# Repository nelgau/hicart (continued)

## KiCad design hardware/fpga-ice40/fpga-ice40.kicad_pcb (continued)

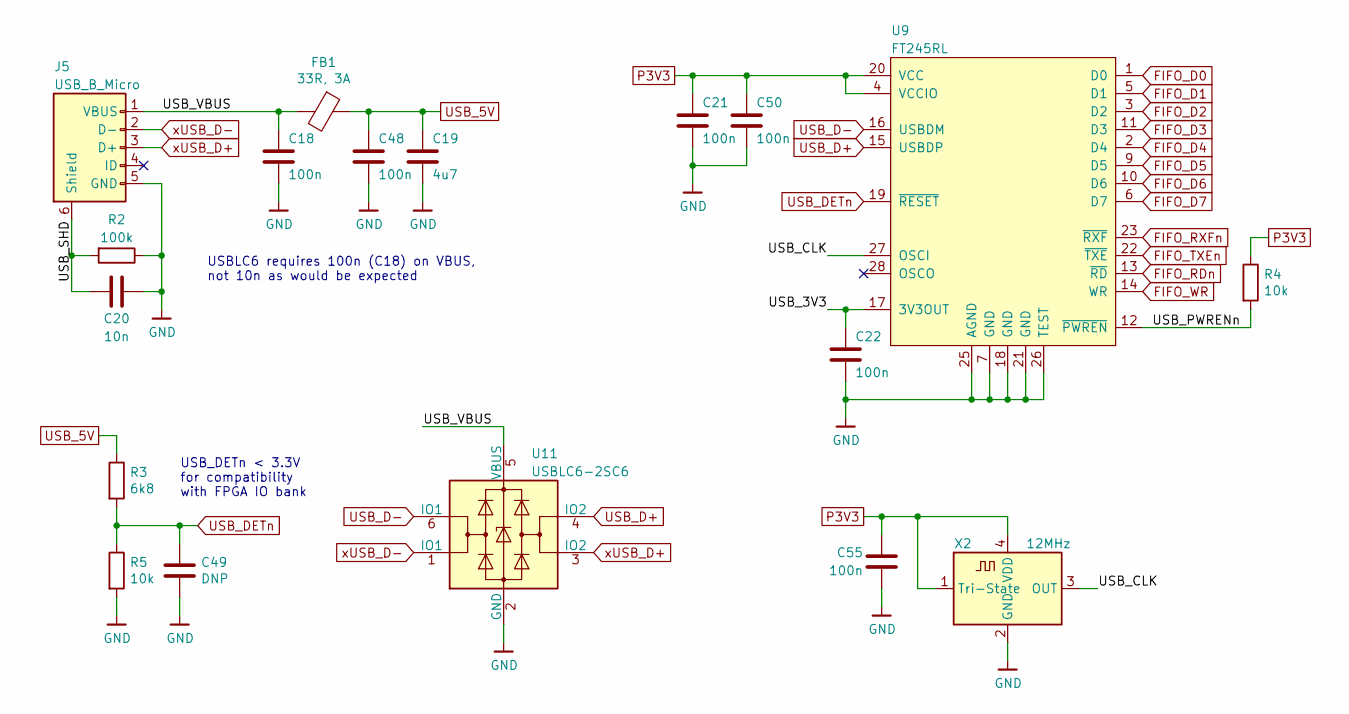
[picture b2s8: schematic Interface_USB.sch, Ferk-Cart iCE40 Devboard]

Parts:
C18, C21, C22, C48, C50, C55: 100n; C_0603_1608Metric; MPN CL10B104KB8NNNC
C19: 4u7; C_0603_1608Metric; MPN CL10A475KA8NQNC
C20: 10n; C_0603_1608Metric; MPN CL10B103KC8NNNC
C49: DNP; C_0603_1608Metric
FB1: 33R, 3A; L_0603_1608Metric; MPN BLM18PG330SN1D
J5: USB_B_Micro; USB_Micro-B_Molex_47346-0001; MPN 47346-0001
R2: 100k; R_0603_1608Metric; MPN RC0603JR-07100KL
R3: 6k8; R_0603_1608Metric; MPN RC0603FR-076K8L
R4, R5: 10k; R_0603_1608Metric; MPN RC0603FR-0710KL
U9: FT245RL; SSOP-28_5.3x10.2mm_P0.65mm; MPN FT245RL-REEL
U11: USBLC6-2SC6; SOT-23-6
X2: 12MHz; Oscillator_2.5x2.0; MPN ECS-2520MV-120-BN-TR

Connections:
/Interface_USB/USB_3V3: C22.1, U9.17 (3V3OUT)
/Interface_USB/USB_CLK: U9.27 (OSCI), X2.3 (OUT)
/Interface_USB/USB_PWRENn: R4.2, U9.12 (~PWREN)
/Interface_USB/USB_SHD: C20.1, J5.6 (Shield), R2.2
/Interface_USB/USB_VBUS: C18.1, FB1.2, J5.1 (VBUS), U11.5 (VBUS)
FIFO_D0: U9.1 (D0); also elsewhere on the board
FIFO_D1: U9.5 (D1); also elsewhere on the board
FIFO_D2: U9.3 (D2); also elsewhere on the board
FIFO_D3: U9.11 (D3); also elsewhere on the board
FIFO_D4: U9.2 (D4); also elsewhere on the board
FIFO_D5: U9.9 (D5); also elsewhere on the board
FIFO_D6: U9.10 (D6); also elsewhere on the board
FIFO_D7: U9.6 (D7); also elsewhere on the board
FIFO_RDn: U9.13 (~RD); also elsewhere on the board
FIFO_RXFn: U9.23 (~RXF); also elsewhere on the board
FIFO_TXEn: U9.22 (~TXE); also elsewhere on the board
FIFO_WR: U9.14 (WR); also elsewhere on the board
GND: C18.2, C19.2, C20.2, C21.2, C22.2, C48.2, C49.2, C50.2, C55.2, J5.5 (GND), R2.1, R5.2, U9.7 (GND), U9.18 (GND), U9.21 (GND), U9.25 (AGND), U9.26 (TEST), U11.2 (GND), X2.2 (GND); also elsewhere on the board
P3V3: C21.1, C50.1, C55.1, R4.1, U9.4 (VCCIO), U9.20 (VCC), X2.1 (Tri-State), X2.4 (VDD); also elsewhere on the board
USB_5V: C19.1, C48.1, FB1.1, R3.1; also elsewhere on the board
USB_D+: U9.15 (USBDP), U11.4 (IO2)
USB_D-: U9.16 (USBDM), U11.6 (IO1)
USB_DETn: C49.1, R3.2, R5.1, U9.19 (~RESET); also elsewhere on the board
xUSB_D+: J5.3 (D+), U11.3 (IO2)
xUSB_D-: J5.2 (D-), U11.1 (IO1)

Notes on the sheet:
USB_DETn < 3.3V for compatibility with FPGA IO bank
USBLC6 requires 100n (C18) on VBUS, not 10n as would be expected

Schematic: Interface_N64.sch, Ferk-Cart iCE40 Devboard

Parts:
C54: 100n; C_0603_1608Metric
J6: Conn_02x20_Odd_Even; PinHeader_2x20_P2.54mm_Horizontal; MPN C124369
RN4, RN5, RN6, RN7, RN8, RN9: 33R, 1%; R_Array_Convex_4x0603; MPN YC164-FR-0733RL

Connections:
GND: C54.2, J6.12, J6.14, J6.16, J6.18, J6.30; also elsewhere on the board
N64_3V3: J6.13, J6.15, J6.17; also elsewhere on the board
N64_AD0: RN4.7 (R2.2); also elsewhere on the board
N64_AD1: RN4.5 (R4.2); also elsewhere on the board
N64_AD2: RN6.7 (R2.2); also elsewhere on the board
N64_AD3: RN6.5 (R4.2); also elsewhere on the board
N64_AD4: RN5.7 (R2.2); also elsewhere on the board
N64_AD5: RN5.5 (R4.2); also elsewhere on the board
N64_AD6: RN7.8 (R1.2); also elsewhere on the board
N64_AD7: RN7.6 (R3.2); also elsewhere on the board
N64_AD8: RN7.5 (R4.2); also elsewhere on the board
N64_AD9: RN7.7 (R2.2); also elsewhere on the board
N64_AD10: RN5.6 (R3.2); also elsewhere on the board
N64_AD11: RN5.8 (R1.2); also elsewhere on the board
N64_AD12: RN6.6 (R3.2); also elsewhere on the board
N64_AD13: RN6.8 (R1.2); also elsewhere on the board
N64_AD14: RN4.6 (R3.2); also elsewhere on the board
N64_AD15: RN4.8 (R1.2); also elsewhere on the board
N64_ALE_H: RN8.5 (R4.2); also elsewhere on the board
N64_ALE_L: RN8.8 (R1.2); also elsewhere on the board
N64_COLD_RESETn: RN9.7 (R2.2); also elsewhere on the board
N64_OS_EVENTn: RN9.8 (R1.2); also elsewhere on the board
N64_READn: RN8.6 (R3.2); also elsewhere on the board
N64_WRITEn: RN8.7 (R2.2); also elsewhere on the board
P3V3: C54.1; also elsewhere on the board
xN64_AD0: J6.39, RN4.2 (R2.1)
xN64_AD1: J6.37, RN4.4 (R4.1)
xN64_AD2: J6.35, RN6.2 (R2.1)
xN64_AD3: J6.33, RN6.4 (R4.1)
xN64_AD4: J6.25, RN5.2 (R2.1)
xN64_AD5: J6.23, RN5.4 (R4.1)
xN64_AD6: J6.21, RN7.1 (R1.1)
xN64_AD7: J6.19, RN7.3 (R3.1)
xN64_AD8: J6.20, RN7.4 (R4.1)
xN64_AD9: J6.22, RN7.2 (R2.1)
xN64_AD10: J6.24, RN5.3 (R3.1)
xN64_AD11: J6.26, RN5.1 (R1.1)
xN64_AD12: J6.34, RN6.3 (R3.1)
xN64_AD13: J6.36, RN6.1 (R1.1)
xN64_AD14: J6.38, RN4.3 (R3.1)
xN64_AD15: J6.40, RN4.1 (R1.1)
xN64_ALE_H: J6.27, RN8.4 (R4.1)
xN64_ALE_L: J6.31, RN8.1 (R1.1)
xN64_COLD_RESETn: J6.5, RN9.2 (R2.1)
xN64_OS_EVENTn: J6.6, RN9.1 (R1.1)
xN64_READn: J6.28, RN8.3 (R3.1)
xN64_WRITEn: J6.32, RN8.2 (R2.1)

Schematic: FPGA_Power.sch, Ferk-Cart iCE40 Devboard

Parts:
C23, C30, C42: 10u; C_0603_1608Metric; MPN CL10A106MQ8NNNC
C24, C46: 1u; C_0603_1608Metric; MPN CL10A105KB8NNNC
C25, C26, C27, C28, C29, C31, C33, C34, C35, C36, C37, C38, C39, C40, C41, C43: 100n; C_0603_1608Metric; MPN CL10B104KB8NNNC
C32: 10u; C_0805_2012Metric; MPN CL21A106KAYNNNE
C45, C47: 10n; C_0603_1608Metric; MPN CL10B103KC8NNNC
D1: ~~800mVf; D_SOD-123F; MPN SBR2M60S1F-7
R6, R7: 100R; R_0603_1608Metric; MPN RC0603FR-07100RL
U1: iCE40HX4K-TQ144; TQFP-144_20x20mm_P0.5mm; MPN iCE40HX4K-TQ144

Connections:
GND: C23.2, C24.2, C25.2, C26.2, C27.2, C28.2, C29.2, C32.2, C33.2, C34.2, C35.2, C36.2, C37.2, C38.2, C39.2, C40.2, C41.2, C45.2, C46.2, C47.2, U1.5 (GND), U1.13 (GND), U1.14 (GND), U1.59 (GND), U1.69 (GND), U1.86 (GND), U1.103 (GND), U1.132 (GND), U1.140 (GND); also elsewhere on the board
P1V2: C23.1, C24.1, C25.1, C26.1, C27.1, C28.1, C45.1, R6.2, R7.2, U1.27 (VCC), U1.40 (VCC), U1.92 (VCC), U1.111 (VCC); also elsewhere on the board
P3V3: C32.1, C33.1, C34.1, C35.1, C36.1, C37.1, C38.1, C39.1, C40.1, C41.1, C46.1, C47.1, D1.2 (A), U1.6 (VCCIO_3), U1.30 (VCCIO_3), U1.46 (VCCIO_2), U1.57 (VCCIO_2), U1.72 (VCC_SPI), U1.89 (VCCIO_1), U1.100 (VCCIO_1), U1.123 (VCCIO_0), U1.131 (VCCIO_0); also elsewhere on the board
VCC2V5: C29.1, D1.1 (K), U1.108 (VPP_2V5)
VCCGND0: C30.2, C31.2, U1.53 (GNDPLL0)
VCCGND1: C42.2, C43.2, U1.127 (GNDPLL1)
VCCPLL0: C30.1, C31.1, R6.1, U1.54 (VCCPLL0)
VCCPLL1: C42.1, C43.1, R7.1, U1.126 (VCCPLL1)

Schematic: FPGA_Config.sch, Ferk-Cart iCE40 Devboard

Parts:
C44: 100n; C_0603_1608Metric; MPN CL10B104KB8NNNC
RN10: 10k; R_Array_Convex_4x0603; MPN YC164-JR-0710KL
U1: iCE40HX4K-TQ144; TQFP-144_20x20mm_P0.5mm; MPN iCE40HX4K-TQ144
U10: MC74HC1G08DTT1G; SOT-23-5; MPN MC74HC1G08DTT1G
X1: 50MHz; Oscillator_2.5x2.0; MPN ECS-2520MV-500-BN-TR

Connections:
CLK_50MHZ: X1.3 (OUT); also elsewhere on the board
CONFIG_CRESETn: RN10.3, U10.2; also elsewhere on the board
CONFIG_MISO|IO1: U1.68 (IOB_106_SDI); also elsewhere on the board
CONFIG_MOSI|IO0: U1.67 (IOB_105_SDO); also elsewhere on the board
CONFIG_SCK: U1.70 (IOB_107_SCK); also elsewhere on the board
CONFIG_SSn: U1.71 (IOB_108_SS); also elsewhere on the board
FLASH_CRESETn: RN10.2, U10.1; also elsewhere on the board
FPGA_CDONE: RN10.1, U1.65 (CDONE); also elsewhere on the board
FPGA_CRESETn: RN10.4, U1.66 (~CRESET_B), U10.4
GND: C44.2, U10.3 (GND), X1.2 (GND); also elsewhere on the board
P3V3: C44.1, RN10.5, RN10.6, RN10.7, RN10.8, U10.5 (VCC), X1.1 (Tri-State), X1.4 (VDD); also elsewhere on the board

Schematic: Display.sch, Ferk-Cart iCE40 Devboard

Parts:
D2, D3, D4, D5, D6, D7: Green; LED_0603_1608Metric; MPN LTST-C190GKT
Q1: 2N7002H-7; SOT-23; MPN 2N7002H-7
R10, R13: 1k; R_0603_1608Metric; MPN RC0603JR-071KL
R11: 1k; R_Array_Convex_4x0603; MPN YC164-JR-071KL

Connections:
FPGA_CDONE: Q1.1 (G); also elsewhere on the board
GND: D3.1 (K), D4.1 (K), D5.1 (K), D6.1 (K), D7.1 (K), Q1.2 (S); also elsewhere on the board
LED_D0: R11.5; also elsewhere on the board
LED_D1: R11.6; also elsewhere on the board
LED_D2: R11.7; also elsewhere on the board
LED_D3: R11.8; also elsewhere on the board
unnamed: D2.1 (K), Q1.3 (D)
unnamed: D2.2 (A), R10.2
unnamed: D3.2 (A), R11.4
unnamed: D4.2 (A), R11.3
unnamed: D5.2 (A), R11.2
unnamed: D6.2 (A), R11.1
unnamed: D7.2 (A), R13.2
P3V3: R10.1, R13.1; also elsewhere on the board

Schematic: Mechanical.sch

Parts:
FID1, FID2: Fiducial; Fiducial_1mm_Mask2mm
SYM1: Nelgau-Logo; Nelgau-Logo_5.2x1.7mm_SilkScreen

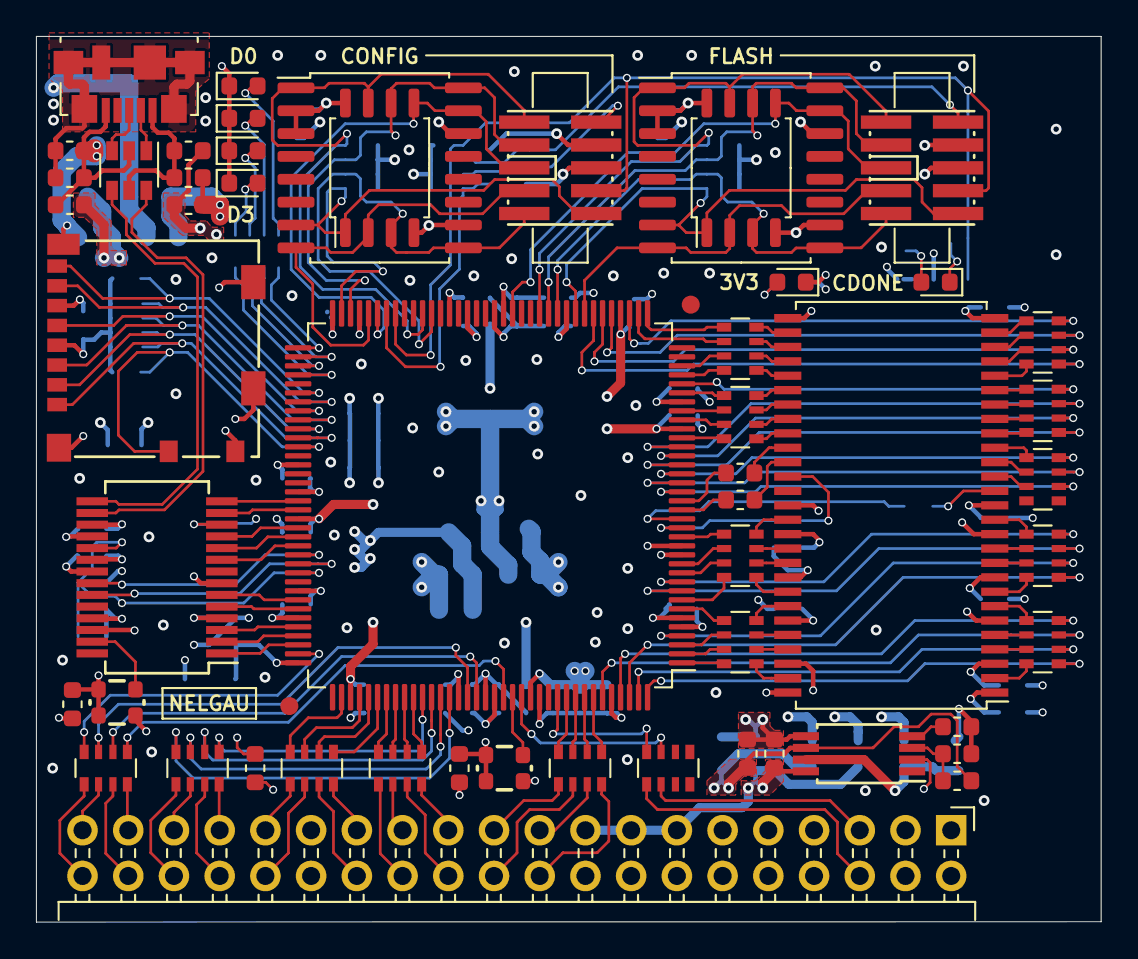
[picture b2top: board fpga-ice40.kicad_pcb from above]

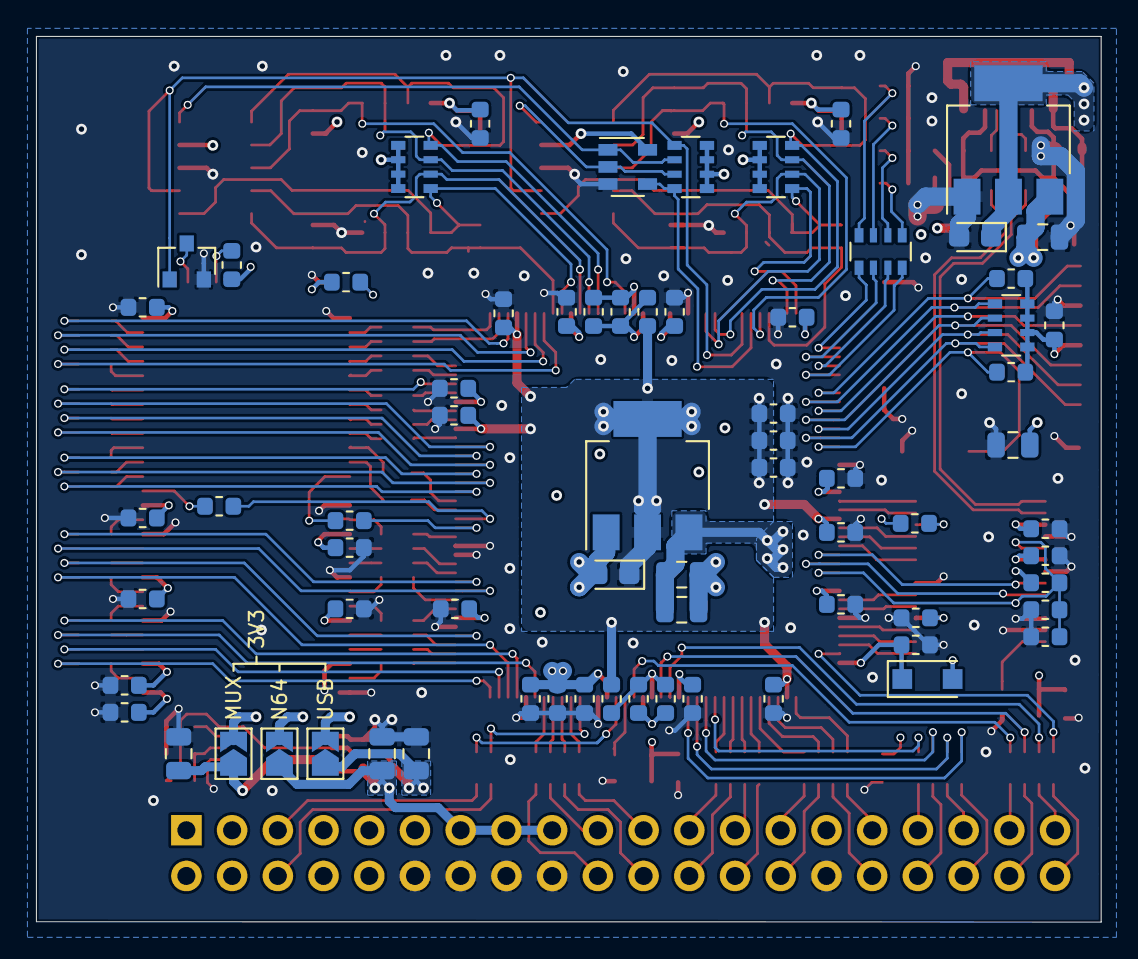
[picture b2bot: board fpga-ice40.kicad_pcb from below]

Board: 4 copper layers, 59.2 x 49.2 mm, 126 parts (70 on the bottom side), 193 nets.

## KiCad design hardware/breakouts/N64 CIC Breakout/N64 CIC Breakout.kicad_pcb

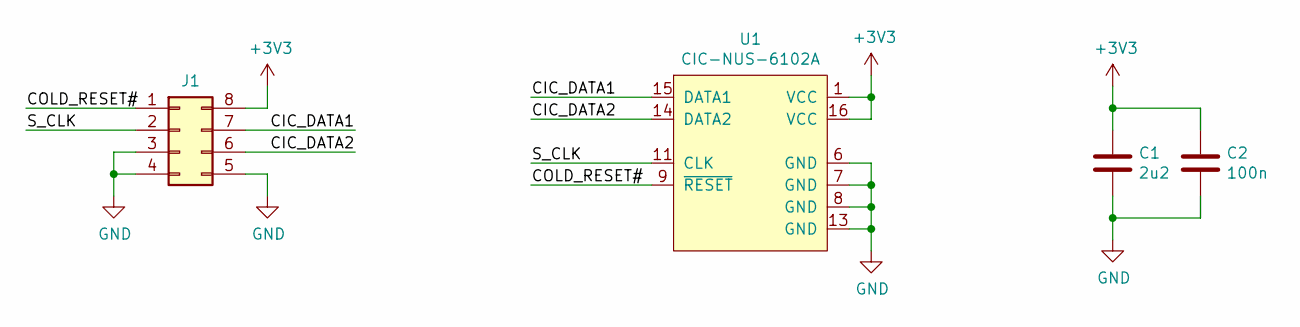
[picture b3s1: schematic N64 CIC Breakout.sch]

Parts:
C1: 2u2; C_0805_2012Metric
C2: 100n; C_0805_2012Metric
J1: Conn_02x04_Counter_Clockwise; PinHeader_2x04_P2.54mm_Horizontal
U1: CIC-NUS-6102A; DIP-16_W7.62mm_Socket

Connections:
+3V3: C1.1, C2.1, J1.8, U1.1 (VCC), U1.16 (VCC)
/CIC_DATA1: J1.7, U1.15 (DATA1)
/CIC_DATA2: J1.6, U1.14 (DATA2)
/COLD_RESET#: J1.1, U1.9 (~RESET)
/S_CLK: J1.2, U1.11 (CLK)
GND: C1.2, C2.2, J1.3, J1.4, J1.5, U1.6 (GND), U1.7 (GND), U1.8 (GND), U1.13 (GND)

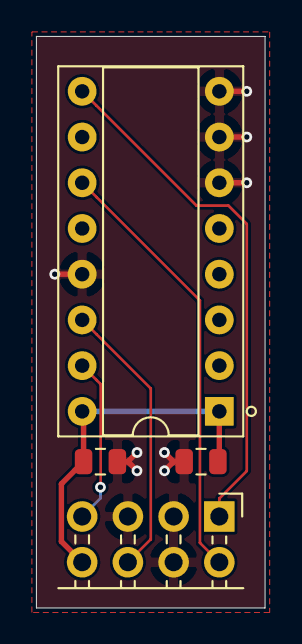
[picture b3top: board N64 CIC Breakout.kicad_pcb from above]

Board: 2 copper layers, 12.7 x 31.8 mm, 4 parts (0 on the bottom side), 6 nets.

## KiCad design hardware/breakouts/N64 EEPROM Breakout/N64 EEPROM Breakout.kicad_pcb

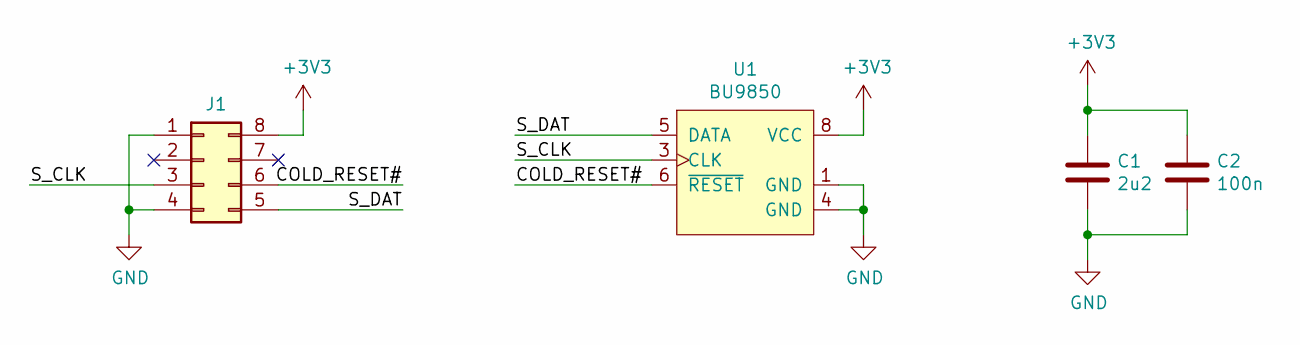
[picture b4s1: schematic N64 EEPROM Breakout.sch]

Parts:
C1: 2u2; C_0805_2012Metric
C2: 100n; C_0805_2012Metric
J1: Conn_02x04_Counter_Clockwise; PinHeader_2x04_P2.54mm_Horizontal
U1: BU9850; DIP-8_W7.62mm_Socket

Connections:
+3V3: C1.1, C2.1, J1.8, U1.8 (VCC)
/COLD_RESET#: J1.6, U1.6 (~RESET)
/S_CLK: J1.3, U1.3 (CLK)
/S_DAT: J1.5, U1.5 (DATA)
GND: C1.2, C2.2, J1.1, J1.4, U1.1 (GND), U1.4 (GND)

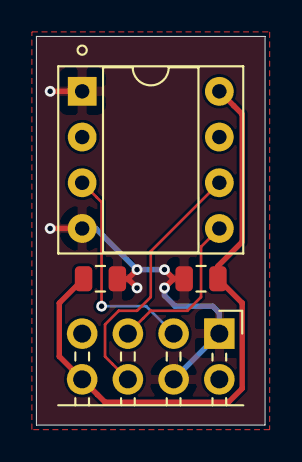
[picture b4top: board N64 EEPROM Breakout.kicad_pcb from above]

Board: 2 copper layers, 12.7 x 21.6 mm, 4 parts (0 on the bottom side), 5 nets.

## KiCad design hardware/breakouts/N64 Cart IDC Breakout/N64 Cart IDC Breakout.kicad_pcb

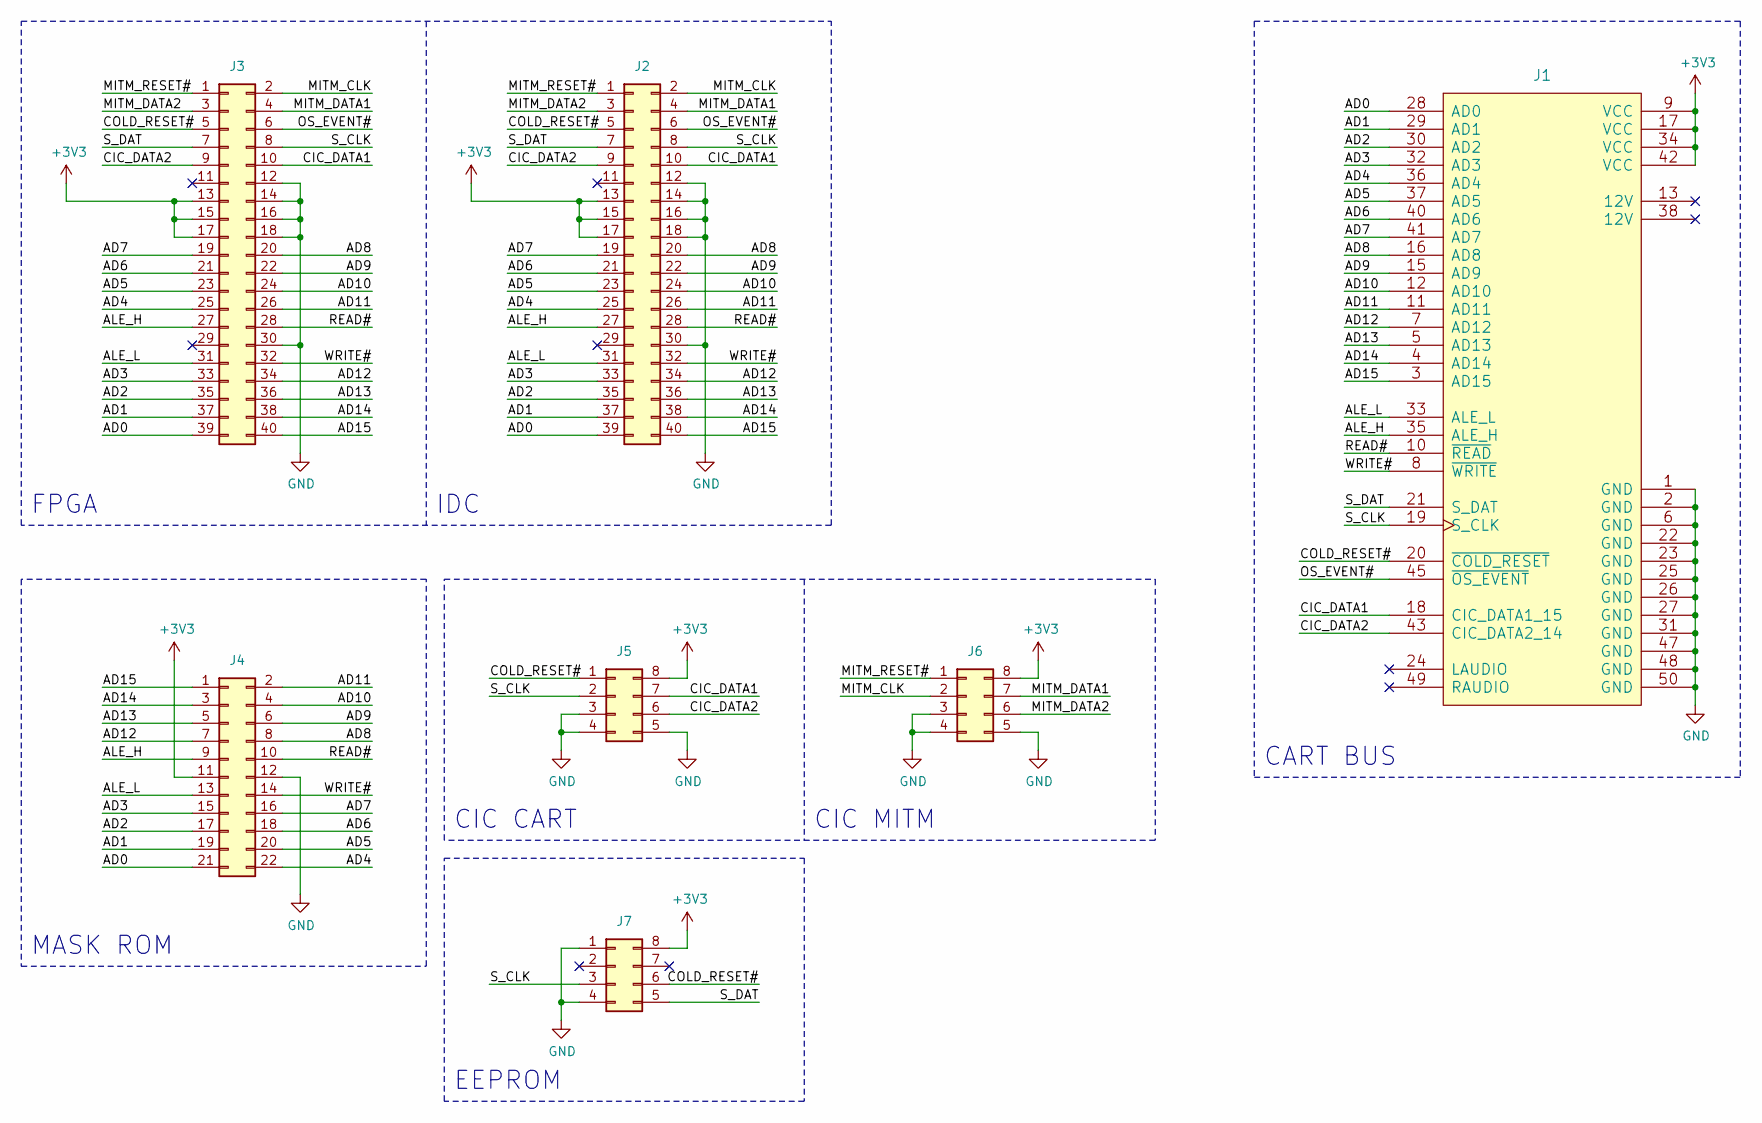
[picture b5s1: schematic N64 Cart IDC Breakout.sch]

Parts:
J1: N64_Cartridge_CardEdge
J2: Conn_02x20_Odd_Even; IDC-Header_2x20_P2.54mm_Vertical
J3: Conn_02x20_Odd_Even; PinSocket_2x20_P2.54mm_Horizontal
J4: Conn_02x11_Odd_Even; PinSocket_2x11_P2.54mm_Horizontal
J5, J6, J7: Conn_02x04_Counter_Clockwise; PinSocket_2x04_P2.54mm_Horizontal

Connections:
+3V3: J1.9 (VCC), J1.17 (VCC), J1.34 (VCC), J1.42 (VCC), J2.13, J2.15, J2.17, J3.13, J3.15, J3.17, J4.11, J5.8, J6.8, J7.8
/AD0: J1.28 (AD0), J2.39, J3.39, J4.21
/AD1: J1.29 (AD1), J2.37, J3.37, J4.19
/AD2: J1.30 (AD2), J2.35, J3.35, J4.17
/AD3: J1.32 (AD3), J2.33, J3.33, J4.15
/AD4: J1.36 (AD4), J2.25, J3.25, J4.22
/AD5: J1.37 (AD5), J2.23, J3.23, J4.20
/AD6: J1.40 (AD6), J2.21, J3.21, J4.18
/AD7: J1.41 (AD7), J2.19, J3.19, J4.16
/AD8: J1.16 (AD8), J2.20, J3.20, J4.8
/AD9: J1.15 (AD9), J2.22, J3.22, J4.6
/AD10: J1.12 (AD10), J2.24, J3.24, J4.4
/AD11: J1.11 (AD11), J2.26, J3.26, J4.2
/AD12: J1.7 (AD12), J2.34, J3.34, J4.7
/AD13: J1.5 (AD13), J2.36, J3.36, J4.5
/AD14: J1.4 (AD14), J2.38, J3.38, J4.3
/AD15: J1.3 (AD15), J2.40, J3.40, J4.1
/ALE_H: J1.35 (ALE_H), J2.27, J3.27, J4.9
/ALE_L: J1.33 (ALE_L), J2.31, J3.31, J4.13
/CIC_DATA1: J1.18 (CIC_DATA1_15), J2.10, J3.10, J5.7
/CIC_DATA2: J1.43 (CIC_DATA2_14), J2.9, J3.9, J5.6
/COLD_RESET#: J1.20 (~COLD_RESET), J2.5, J3.5, J5.1, J7.6
/MITM_CLK: J2.2, J3.2, J6.2
/MITM_DATA1: J2.4, J3.4, J6.7
/MITM_DATA2: J2.3, J3.3, J6.6
/MITM_RESET#: J2.1, J3.1, J6.1
/OS_EVENT#: J1.45 (~OS_EVENT), J2.6, J3.6
/READ#: J1.10 (~READ), J2.28, J3.28, J4.10
/S_CLK: J1.19 (S_CLK), J2.8, J3.8, J5.2, J7.3
/S_DAT: J1.21 (S_DAT), J2.7, J3.7, J7.5
/WRITE#: J1.8 (~WRITE), J2.32, J3.32, J4.14
GND: J1.1 (GND), J1.2 (GND), J1.6 (GND), J1.22 (GND), J1.23 (GND), J1.25 (GND), J1.26 (GND), J1.27 (GND), J1.31 (GND), J1.47 (GND), J1.48 (GND), J1.50 (GND), J2.12, J2.14, J2.16, J2.18, J2.30, J3.12, J3.14, J3.16, J3.18, J3.30, J4.12, J5.3, J5.4, J5.5, J6.3, J6.4, J6.5, J7.1, J7.4

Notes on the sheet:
FPGA
IDC
CIC CART
CIC MITM
MASK ROM
EEPROM
CART BUS

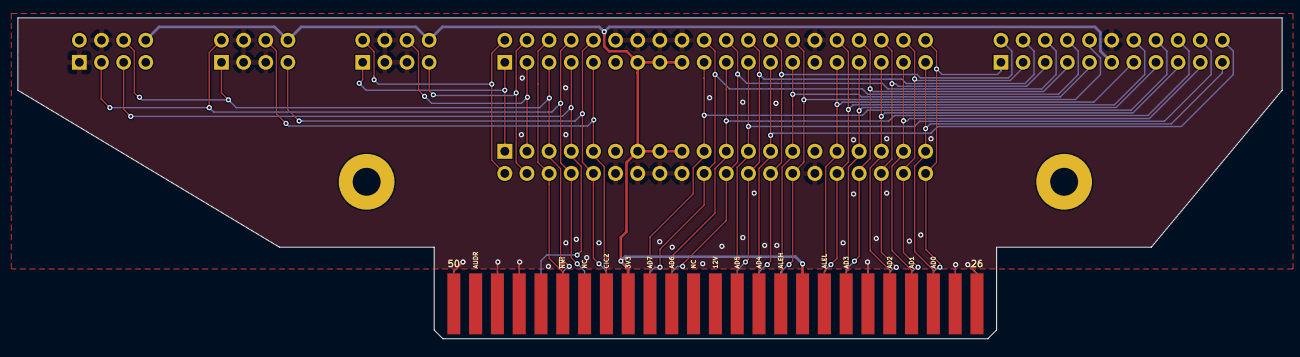
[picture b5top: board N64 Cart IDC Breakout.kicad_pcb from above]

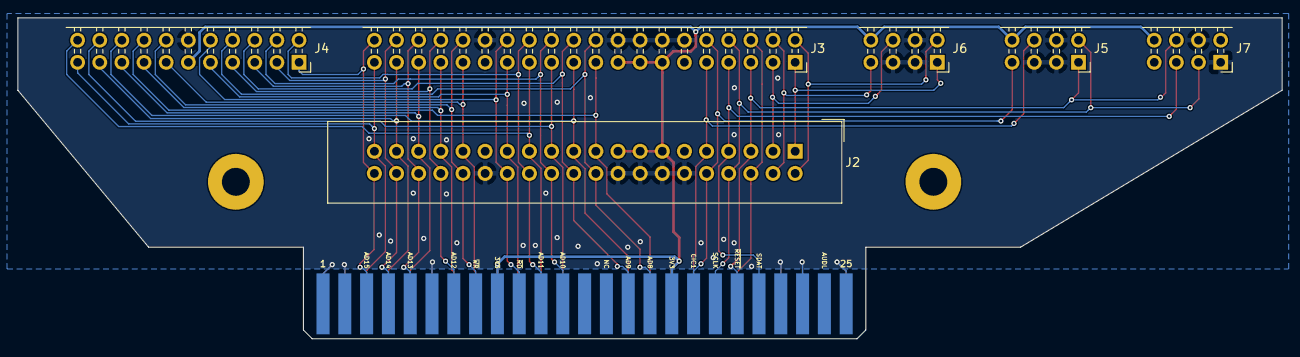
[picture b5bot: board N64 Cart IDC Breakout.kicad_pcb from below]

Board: 2 copper layers, 145.0 x 36.8 mm, 9 parts (6 on the bottom side), 32 nets.

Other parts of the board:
M1, M2: MountingHole_3.2mm_M3_Pad

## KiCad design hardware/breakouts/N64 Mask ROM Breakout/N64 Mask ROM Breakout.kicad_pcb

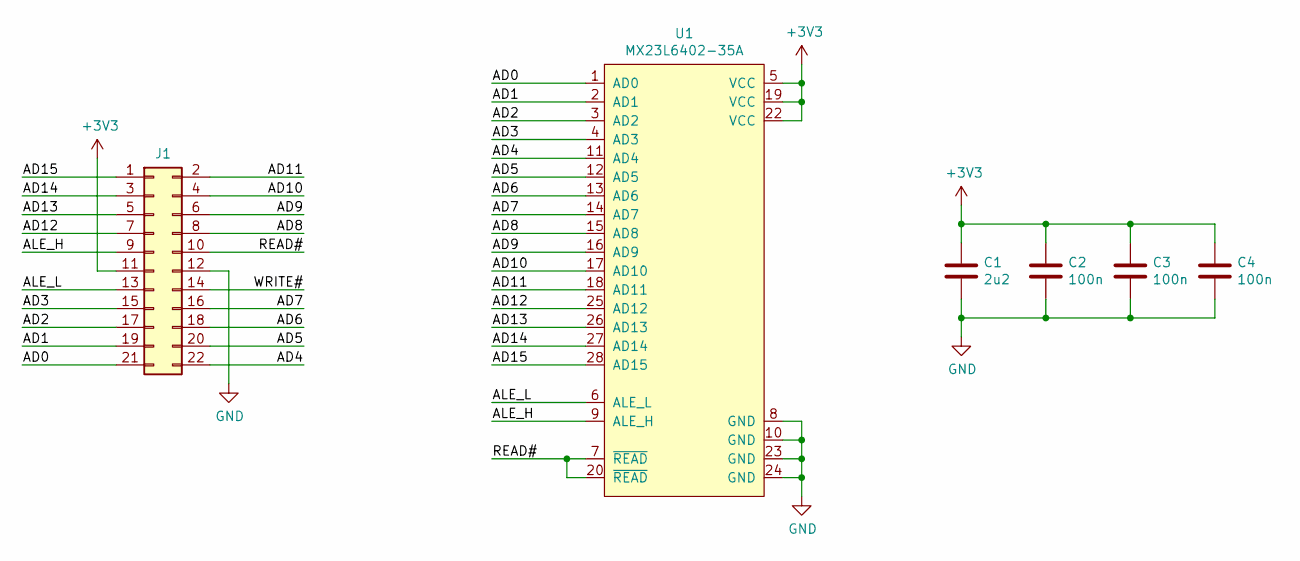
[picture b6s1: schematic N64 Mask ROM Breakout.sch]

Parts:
C1: 2u2; C_0805_2012Metric
C2, C3, C4: 100n; C_0805_2012Metric
J1: Conn_02x11_Odd_Even; PinHeader_2x11_P2.54mm_Horizontal
U1: MX23L6402-35A; DIP-28_W15.24mm_Socket

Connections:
+3V3: C1.1, C2.1, C3.1, C4.1, J1.11, U1.5 (VCC), U1.19 (VCC), U1.22 (VCC)
/AD0: J1.21, U1.1 (AD0)
/AD1: J1.19, U1.2 (AD1)
/AD2: J1.17, U1.3 (AD2)
/AD3: J1.15, U1.4 (AD3)
/AD4: J1.22, U1.11 (AD4)
/AD5: J1.20, U1.12 (AD5)
/AD6: J1.18, U1.13 (AD6)
/AD7: J1.16, U1.14 (AD7)
/AD8: J1.8, U1.15 (AD8)
/AD9: J1.6, U1.16 (AD9)
/AD10: J1.4, U1.17 (AD10)
/AD11: J1.2, U1.18 (AD11)
/AD12: J1.7, U1.25 (AD12)
/AD13: J1.5, U1.26 (AD13)
/AD14: J1.3, U1.27 (AD14)
/AD15: J1.1, U1.28 (AD15)
/ALE_H: J1.9, U1.9 (ALE_H)
/ALE_L: J1.13, U1.6 (ALE_L)
/READ#: J1.10, U1.7 (~READ), U1.20 (~READ)
/WRITE#: J1.14
GND: C1.2, C2.2, C3.2, C4.2, J1.12, U1.8 (GND), U1.10 (GND), U1.23 (GND), U1.24 (GND)

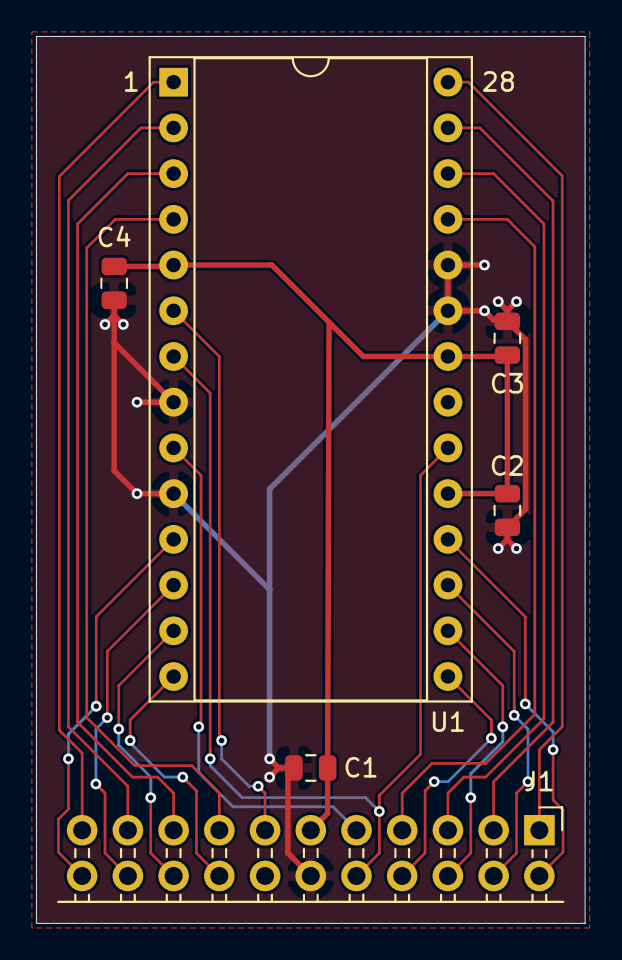
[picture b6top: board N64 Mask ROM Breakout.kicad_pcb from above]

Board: 2 copper layers, 30.5 x 49.3 mm, 6 parts (0 on the bottom side), 21 nets.

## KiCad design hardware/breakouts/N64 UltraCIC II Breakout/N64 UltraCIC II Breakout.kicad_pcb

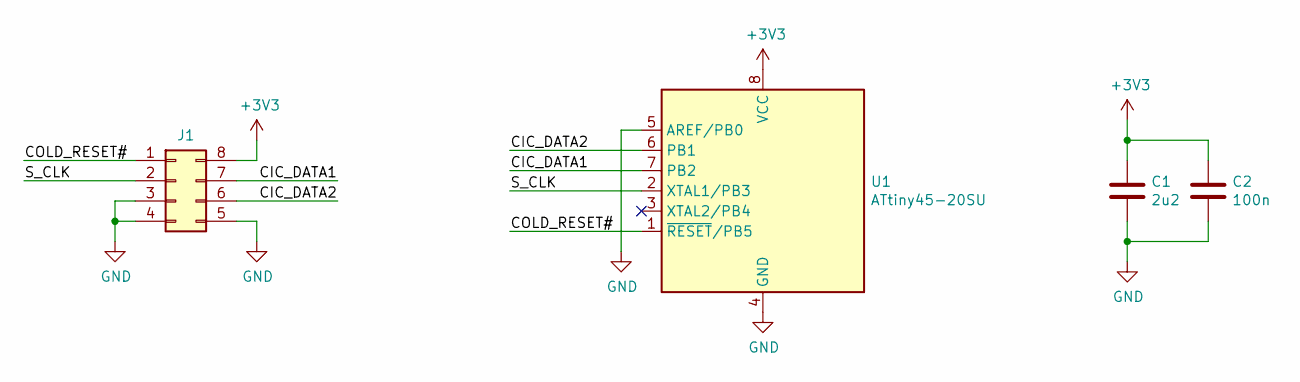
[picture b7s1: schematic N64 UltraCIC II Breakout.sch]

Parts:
C1: 2u2; C_0805_2012Metric
C2: 100n; C_0805_2012Metric
J1: Conn_02x04_Counter_Clockwise; PinHeader_2x04_P2.54mm_Horizontal
U1: ATtiny45-20SU; SOIJ-8_5.3x5.3mm_P1.27mm

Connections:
+3V3: C1.1, C2.1, J1.8, U1.8 (VCC)
/CIC_DATA1: J1.7, U1.7 (PB2)
/CIC_DATA2: J1.6, U1.6 (PB1)
/COLD_RESET#: J1.1, U1.1 (~RESET~/PB5)
/S_CLK: J1.2, U1.2 (XTAL1/PB3)
GND: C1.2, C2.2, J1.3, J1.4, J1.5, U1.4 (GND), U1.5 (AREF/PB0)

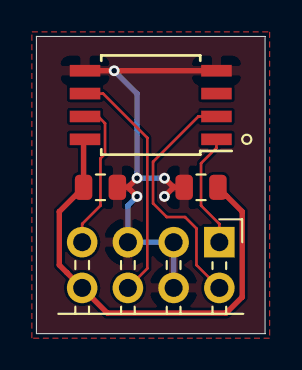
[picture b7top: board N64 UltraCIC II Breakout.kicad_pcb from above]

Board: 2 copper layers, 12.7 x 16.5 mm, 4 parts (0 on the bottom side), 6 nets.

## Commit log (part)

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2020-11-29 Update 'nelgau' library
2020-11-29 Substitute QE=1 config flash to keep boot time as short as possible
2020-11-29 Add configuration done LED
2020-11-30 Add power rail test points to schematic
2020-11-30 Fix the configuration flash's decoupling capacitor
2020-11-30 Add testpoints for clock oscillator outputs
2020-11-30 Layout testpoints for power rails and clock oscillators
2020-12-04 Connect feedback testpoints to resistor divider
2021-01-03 Use 0402 package for all 4u7 bypass capacitors
2021-01-06 Don't stuff the net name into test point values
2021-01-06 Enlarge test points to 1mm diameter
2021-01-06 Clarify pull-up design for configuration flash and FPGA reset signal
2021-01-06 Add header for injecting 3V3 rail without populating USB_3V3 regulator and power mux
2021-01-22 Reassign symbols that were rescued during update
2021-01-24 Assign MPN for all other components except oscillators
2021-01-25 Connect FT2232HQ center pad to ground
2021-01-25 Added a copper poor for the sheild of the USB connector
2021-01-26 Update PCB is reflect changes to schematic
2021-01-29 Place 1u decoupling caps near hyperram
2021-01-29 Assign MPN for hyperram device
2021-01-29 Add ground test point for hyperram interface
2021-01-30 Replace 2.5x2.0mm oscillators with SiT2001B SOT23-5 oscillators
2021-01-30 Set solder paste absolute clearance to 0
2021-01-30 Add zones for USB_3V3 and N64_3V3 terminations
2021-01-30 Output production gerbers for RevA
2021-01-30 Regenerate revA gerbers
2022-01-29 Import gateware and firmware from the minerva-test repo
2022-01-29 Ignore traces/ directory for now
2022-01-29 Clarify ecppack_opts override
2022-01-30 Reenable main CIC output test
2022-01-30 Update README with new name and hero image
2022-01-30 Use PLL generator instead of hardcoding EHXPLLL values
2022-01-30 Move ECP5PLL generator to vendor dir
2022-04-14 Correct typo during vendoring of ECP5PLL generator
2022-10-05 Fix lambdasoc bios submodule cloning issue
    This commit forks lambdasoc and updates its lambdasoc-bios submodule to HEAD.
    A submodule of lambdasoc, lambdasoc-bios, itself includes a submodule from
    the git.llvm.org hierarchy, compiler_rt. After the LLVM project moved its
    repositories to Github, this reference has rotted into a redirect loop. The
    issue was fixed in lambdasoc-bios. Unfortunately, lambdasoc hasn't yet been
    updated to reference the fix.
2022-10-05 Downgrade libusb1 to 1.9.3, the last non-yanked version before 2.0.0
2022-10-05 Add cocotb and cocotb-test dependencies
2022-10-06 Update pytest to fix assertion issue under Py3.10
    See https://github.com/pytest-dev/pytest/issues/8539
2022-10-06 Provisionary test harness based on amaranth-cocotb
2022-10-06 Update nextpnr-ecp5 build time estimate
2022-10-06 Rename README.rst to README.md
2022-10-06 Document icarus-verilog package dependency
2022-10-06 Add instructions to build python with --enable-shared
2022-10-06 Simplify cocotb-test runner as we don't need to subclass Icarus
2022-10-06 Empty out synonyms in the hicart.test module root
2022-10-06 Fix failing test in hicart.n64.pi
    The initiator's wishbone bus uses the stall feature. To be connectable, the
    DUT's decoder needs to support that feature as well.
2022-10-06 Fix failing test in hicart.n64.ad16
    The Pysim-style test cases for this module predate the implementation of
    the deep synchronizer for the address-data lines. Additionally, on read,
    the high and low words were swapped, as presented to the AD16 bus.
    These failures are a good argument for why it must be possible to run
    the entire test suite easily and with a single command.
2022-10-06 Divide the test infrastructure into pysim and cocotb modules
2022-10-06 Don't generate waveforms unless GENERATE_VCDS is set
2022-10-06 Improve cocotb test harness readability
2022-10-07 Add enjoydigital/litesdcard dependency
2022-10-07 Begin to integrate lambdaconcept's LiteX core wrapper idea
2022-10-07 Slightly hacky way to generate i/o/oe-style IO
2022-10-08 Passthrough SD interface pins to LiteSDCard core instance
2022-10-08 Move litesdcard generator to vendor directory
2022-10-10 Remove of the module name introspection magic from cocotb testcases
2022-10-10 Validate cocotb test concept with a basic AD16 driver coroutine
2022-10-10 Simulate the platform's qspi clock gating in the cocotb tests
2022-10-10 Factor out trace list flattening
2022-10-10 Adds PIInitiator cocotb driver modeled after the Pysim driver
2022-10-10 Use an adapter to access amaranth records in cocotb tests
2022-10-10 Light refactor to make it easier to lift accessors out of tests
2022-10-11 Pass Home Invader platform into the cocotb runner
2022-10-11 May need to build path to generated verilog file
2022-10-12 Testbench to debug combinatorial loop in litesdcard
2022-10-12 Update README to point to hero image itself
2022-10-12 Fix for when {build,traces} directories exist
2022-10-12 A makefile is the proper tool for this job
2022-10-12 Update debugging log
2022-10-12 Add new findings to debug log
2022-10-12 Solved the iverilog combinatorial loop
    Simulators, such as Icarus Verilog and Verilator, require a diffferent
    style of combinatorial loop. Adding the `regular_comb=False` generates
    simulation-compatible combinatoral logic. This is required by LiteDRAM
    as well, suggesting the issue plagues more than just LiteSDCard.
    Enjoy-Digital also recommended this fix for combinatorial simulation
    loop in this Twitter thread:
2022-10-13 Add wishbone_accessor
2022-10-13 Fix pyproject.toml whitespace
2022-10-14 Integrate cocotb wishbone master
2022-10-15 Build out arbiter-decoder structure for litesdcard test
2022-10-15 Cleanup domain initialization and reset
2022-10-15 Add a quick way to print the generated verilog
2022-10-20 Fully-qualify the names of tapped packages
2022-10-29 Add Makefile for gateware subproject
2022-10-30 Add subproject for libdragon-based cart software
2022-10-30 Add .gitkeep for roms/
2022-10-30 Script for launching cart software in ares
2022-10-30 software: Add target for launching cart in ares
2022-10-30 roms: Move .gitignore into subproject folder
2022-10-30 hardware: Move .gitignore into subproject folder
2022-10-30 gateware: Move .gitignore in subproject folder
2022-10-31 software: Remove upstream libdragon submodule
2022-10-31 software: Add nelgau/libdragon fork as a submodule
2022-10-31 software: Switch libdragon to rasky/gfx-rdp branch
2022-10-31 soft: Keep the outer makefile silent
2022-10-31 soft: Makefile style
2022-10-31 soft: More makefile style
2022-10-31 soft: Extremely simple filesystem demo
2022-10-31 media: Encode m1v video (no audio) for now
2022-10-31 soft: Basic video decoding
2022-11-08 poetry: Keep venv in project directory
2022-11-08 pyright: Initial settings
2022-11-08 pyright: Disable type-checking
    Amaranth isn't type-hinted and the errors are very distracting.
2023-09-12 gate: Workaround for IRQLine/SignalMeta incompatibility
2023-09-12 gate: Pin instances can no longer be cast to value directly
2023-09-15 Add script to set the power switch state
2023-09-15 gate: Decouple build and program, and add power cycling
2023-09-15 gate: Independent targets for writing bitstream to SRAM and flash
2023-09-15 soft: Target for programming flash
2023-09-15 gate: Clean up Makefile
2023-09-15 Create Makefile for root project
2023-09-15 media: Video decoder expects width % 32 == 0
2023-09-15 soft: Use conforming test video file for now
2023-09-16 soft: Disable isviewer and usblog, gateware is incompatible?
2023-09-16 soft: Loop video forever
2023-09-16 soft: Use a loop that makes me happy
2023-09-17 gate: Bump amaranth ref
2023-09-17 gate: Add pre-lib.wiring override for amaranth-soc
2023-09-19 gate: Remove lambdasoc and litedram dependencies
2023-09-19 gate: Pull in only the parts of lambdasoc we really need
2023-09-19 gate: Fix IRQLine for litesdcard core test
2023-09-25 gate: Fix incorrect granularity of the burst and wishbone buses
2023-09-25 gate: Update amaranth-soc for initial lib.wiring migration
2023-09-25 gate: Migrate AD16 and cart wishbone interfaces to lib.wiring
2023-09-26 gate: Migrate CIC to lib.wiring
2023-09-27 gate: Pick up flipped signature fix from nelgau/amaranth
2023-09-27 gate: Migrate QSPI flash interface to lib.wiring
2023-09-27 gate: Fix read integration test
2023-09-27 gate: Fix for signature flipping is now upstream
2023-09-28 gate: Read integration test should use the correct clock speed
2023-09-28 gate: QSPI shouldn't use a TristateSignature for its data bus
2023-09-28 gate: Remove dead code from read integration test
2023-09-29 gate: Add interface for cartridge bus
2023-09-29 gate: Add new pi wishbone bridge
2023-09-29 gate: Migrate read integration test to new pi bridge
2023-09-29 gate: Migrate hicart top to new pi bridge
2023-09-29 gate: Replace old pi bridge
2023-09-29 gate: Vacuous fixes for cocotb and litesdcard tests
2023-10-01 gate: Standardize on driver and emulator nomenclature
2023-10-04 gate: Nest signals in N64 cart bus resource
2023-10-04 gate: Use new-style vendor platform import
2023-10-06 gate: Migrate peripherals away from old lambdasoc package
2023-10-06 gate: Remove old lambdasoc components
2023-10-06 gate: Create dynamic signatures with memory maps
2023-10-06 gate: Pass memory map into interface constructor
2023-10-06 gate: Use signal in place of IRQLine
2023-10-06 gate: Move back to amaranth-soc@main, lib.wiring components were merged
2023-10-12 gate: Update amaranth-soc
2023-10-20 gate: Use CICSignature class in CIC component
2023-10-20 gate: Correct signal names in CIC component
2023-10-21 gate: Silence record-related deprecation warnings
2023-10-21 gate: Clean up comb logic in CIC component
2023-10-21 gate: Make cartbus signatures connectable to pins
2023-10-22 gate: Migrate FT245 controller to lib.wiring
2023-10-22 gate: Migrate FT245Interface consumers to lib.wiring
2023-10-22 gate: Improve constants
2023-10-22 gate: Fix ILA interactive display with personal gtkwave wrapper
2023-10-22 gate: Improve netlist size and speed
2023-10-26 gate: Clean up Minerva component
2024-02-29 software: libdragon unstable -> preview
2024-02-29 software: Update libdragon npm package
2024-02-29 software: Pin libdragon to avoid recent YUV bug
2024-03-01 gateware: Pin packages for migration
2024-03-26 gateware: Don't pollute repo with PDM's temporary files
2024-03-26 gateware: Clean up .pdm-build directory too
2024-03-26 gateware: Migration progress, tests passing
2024-03-27 gateware: Manually wire components to FPGA pins during migration
2024-03-27 gateware: Pin minerva to main
2024-03-28 gateware: Roll forward to just before RFC 43 implementation
2024-03-30 hardware: Update .gitignore for KiCad 8
2024-04-01 hardware: Update 'nelgau' library from legacy format
2024-04-03 hardware: Use environment variable to locate nelgau libs
2024-04-06 Re-add personal KiCad libraries as nelgau-kicad-lib
2024-04-06 Locate personal libraries within project directory
2024-04-10 gate: Upgrade amaranth to v0.4.5
2024-04-26 hardware: Substitute library symbol for ATtiny microcontroller
2024-04-27 hardware: Substitute library symbol for ferrite bead
2024-04-28 hardware: Substitute library symbol for USBLC6
2024-04-29 hardware: Update 'nelgau' library
2024-04-30 hardware: Update PCB from schematic after migration to v8
2024-05-01 hardware: Remove superfluous vias near card edge connector
2024-05-02 hardware: Fix swapped USB nets on schematic
2024-05-03 hardware: Adjust copper to hole clearance for BGA breakout
2024-05-05 hardware: Fix USB connector NPTH clearance
2024-05-08 hardware: Connect USB shield by thermal reliefs
2024-05-09 hardware: Fix silkscreen overlapping board edge
2024-05-10 hardware: Reduce minimum text height
2024-05-11 hardware: Substitute library footprint for WSON-8-1EP
2024-05-12 hardware: Substitute library footprint for TSSOP-8
2024-05-13 hardware: Substitute library footprint for 0402 capacitors
2024-05-14 hardware: Substitute library footprint for 0402 resistors
2024-05-16 hardware: Substitute library footprint for 0805 inductors
2024-05-17 hardware: Substitute library footprint for SOT-23-5
2024-05-18 hardware: Substitute library footprint for SOT-23-6
2024-05-19 hardware: Substitute library footprint for SOT-323/SC-70
2024-05-20 hardware: Solve clearances for USB serial EEPROM
2024-05-22 hardware: Solve clearances for USB_3V3 regulator
2024-05-23 hardware: Solve clearances for P1V1 regulator
